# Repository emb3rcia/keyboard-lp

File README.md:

# keyboard-lp

## Description

It is my first low-profile keyboard, and first per-key GPIO keyboard. It features 2 USB ports - one for communication with PC and one for power for LEDs, per-key LED backlight and full n-key rollover!

## Why i made this project

I like making keyboards, it is my second keyboard i designed and it is very fun. I also want to use LP keyboard, but i dont have budget to buy ready-to-use one.

## What i learned

Mainly i learned even more about tight connection layout on PCB, as with per-key GPIO i needed to connect each key to its individual pin on MCU.

# Photos

# BOM

|Product                            |Description                    |Price   |Shipping                               |Amount      |Why more than needed               |Link                                              |
|-----------------------------------|-------------------------------|--------|---------------------------------------|------------|-----------------------------------|--------------------------------------------------|
|Kalih Choc v2                      |Switches                       |27.72USD|Free                                   |90          |Nearest amount more to 87 needed   |https://aliexpress.com/item/1005008175864256.html |
|Keycaps                            |Keycaps                        |14.89USD|Free                                   |118         |Its full set, cheapest I could find|https://aliexpress.com/item/1005004613625285.html |
|Stabs                              |Stabilizers                    |6.10USD |Free                                   |1x6.25u 4x2u|N/A                                |https://aliexpress.com/item/1005009331747192.html |
|TORCH C0805B104K500NT              |Decoup caps                    |0.43USD |LCSC                                   |125         |Sold in batches of 25, need 101    |https://www.lcsc.com/product-detail/C476766.html  |
|Taiyo Yuden HMK212BC7105KGHTE      |Bigger decoup caps             |0.43USD |LCSC                                   |10          |Sold in batches of 10, need 9      |https://www.lcsc.com/product-detail/C385977.html  |
|KEMET C0805C473J3GECTU             |Bulk decoup caps               |1.04USD |LCSC                                   |5           |Sold in batches of 5, need 2       |https://www.lcsc.com/product-detail/C22409503.html|
|TECH PUBLIC RCLAMP0502BATCT        |ESD diode for CC and Data lanes|0.48USD |LCSC                                   |10          |Sold in batches of 10, need 3      |https://www.lcsc.com/product-detail/C3040620.html |
|TI SN74LVC1T45DCKR                 |Level shifter                  |0.45USD |LCSC                                   |5           |Sold in batches of 5, need 1       |https://www.lcsc.com/product-detail/C9382.html    |
|SHOU HAN TYPE-C 16PIN 2MD(073)     |USB-C ports                    |1.23USD |LCSC                                   |20          |Sold in batches of 20, need 2      |https://www.lcsc.com/product-detail/C2765186.html |
|MICROCHIP MCP1726-3302E/SN         |LDO                            |2.22USD |LCSC                                   |1           |N/A                                |https://www.lcsc.com/product-detail/C635928.html  |
|OPSCO Optoelectronics SK6812MINI-YW|LED Diodes                     |14.85USD|LCSC                                   |90          |Sold in batches of 5, need 87      |https://www.lcsc.com/product-detail/C5378722.html |
|Littelfuse SMA6L5.0A               |VBUS ESD diodes                |1.57USD |LCSC                                   |2           |N/A                                |https://www.lcsc.com/product-detail/C1974860.html |
|FOJAN FRC0805J220 TS               |Data lanes resistors           |0.17USD |LCSC                                   |100         |Sold in batches of 100, need 2     |https://www.lcsc.com/product-detail/C2907310.html |
|FOJAN FRC0805J330 TS               |Level shifter→LEDs resistor    |0.17USD |LCSC                                   |100         |Sold in batches of 100, need 1     |https://www.lcsc.com/product-detail/C2907322.html |
|FOJAN FRC0805J103TS                |Boot pin pulldown resistor     |0.18USD |LCSC                                   |100         |Sold in batches of 100, need 1     |https://www.lcsc.com/product-detail/C2930231.html |
|FOJAN FRC0805J512TS                |CC resistors                   |0.17USD |LCSC                                   |100         |Sold in batches of 100, need 2     |https://www.lcsc.com/product-detail/C2930296.html |
|ST STM32G474QCT6                   |MCU                            |7.30USD |LCSC  (5.07USD for all items from LCSC)|1x6.25u 4x2u|N/A                                |https://www.lcsc.com/product-detail/C730128.html  |
|PCB from JLCPCB                    |PCB                            |54.40USD|19.14USD                               |5           |Minimal order is 5                 |https://www.jlcpcb.com                            |
|Screws                             |M2x12 flathead screws          |1.48USD |Free                                   |50          |Minimal order is 50                |https://aliexpress.com/item/1005007593731439.html |
|Total                              |97.79USD                       |74.58USD|25.21USD                               |            |                                   |                                                  |

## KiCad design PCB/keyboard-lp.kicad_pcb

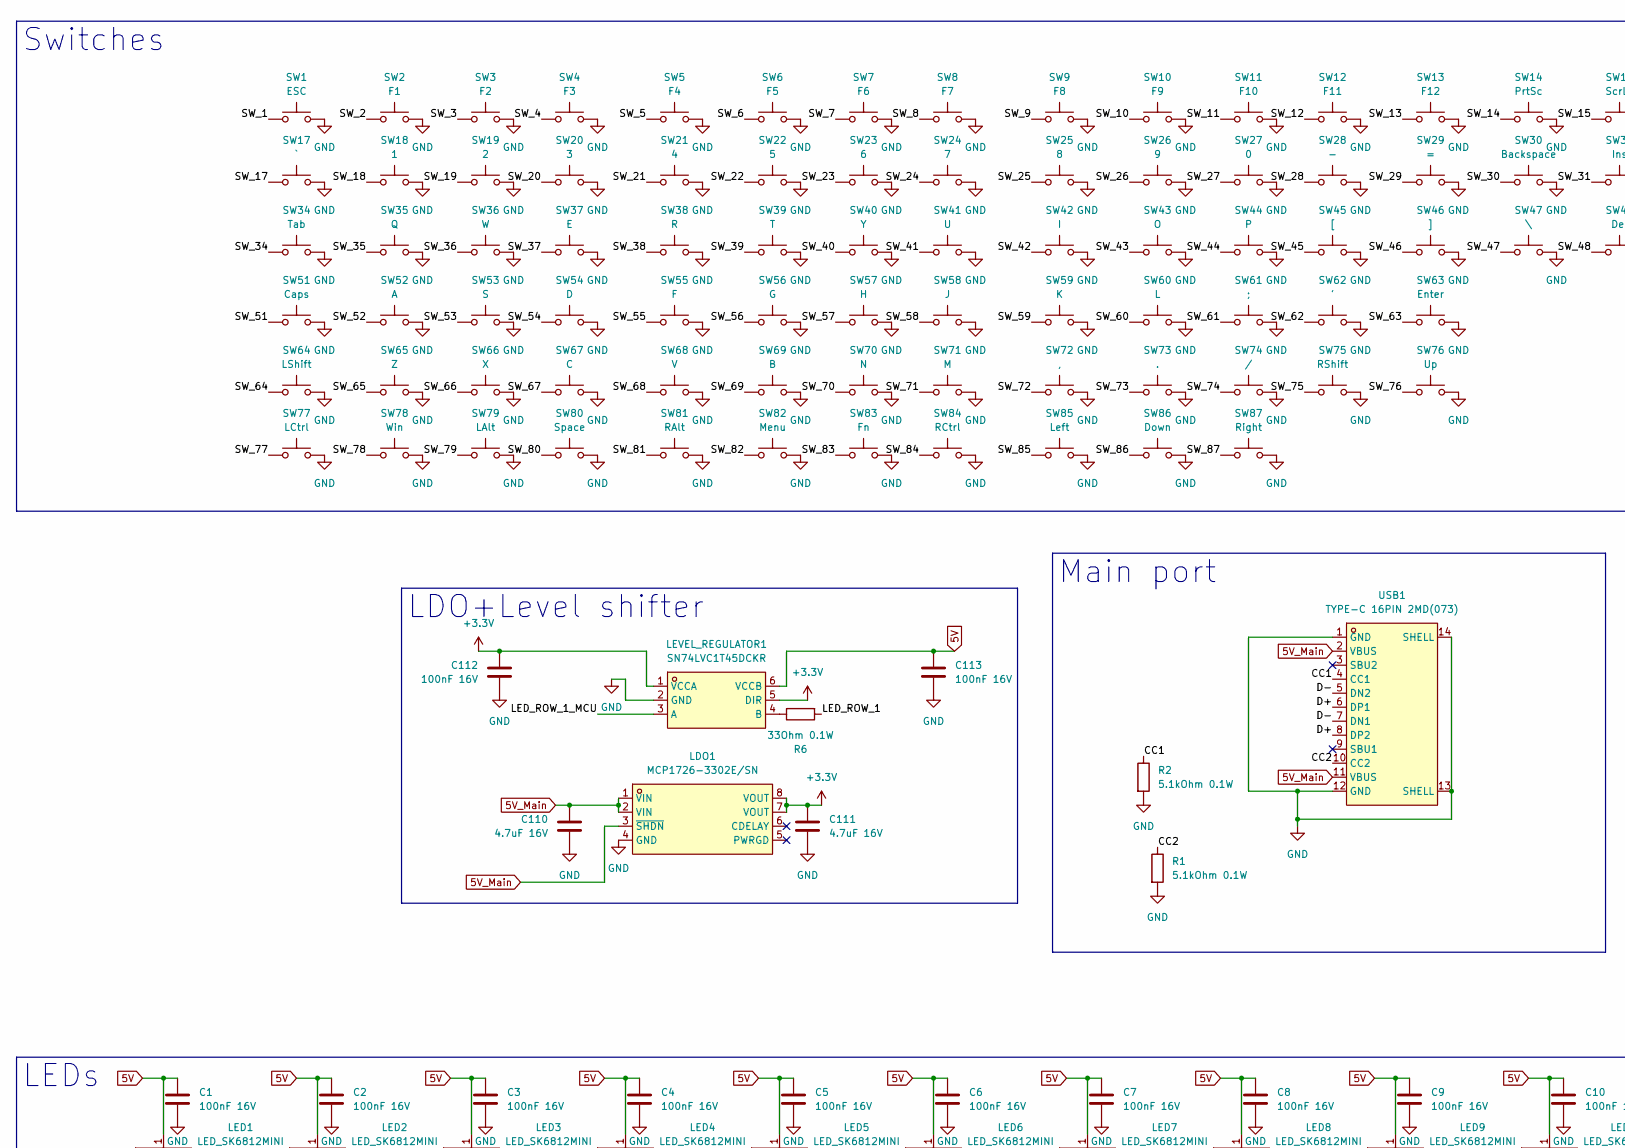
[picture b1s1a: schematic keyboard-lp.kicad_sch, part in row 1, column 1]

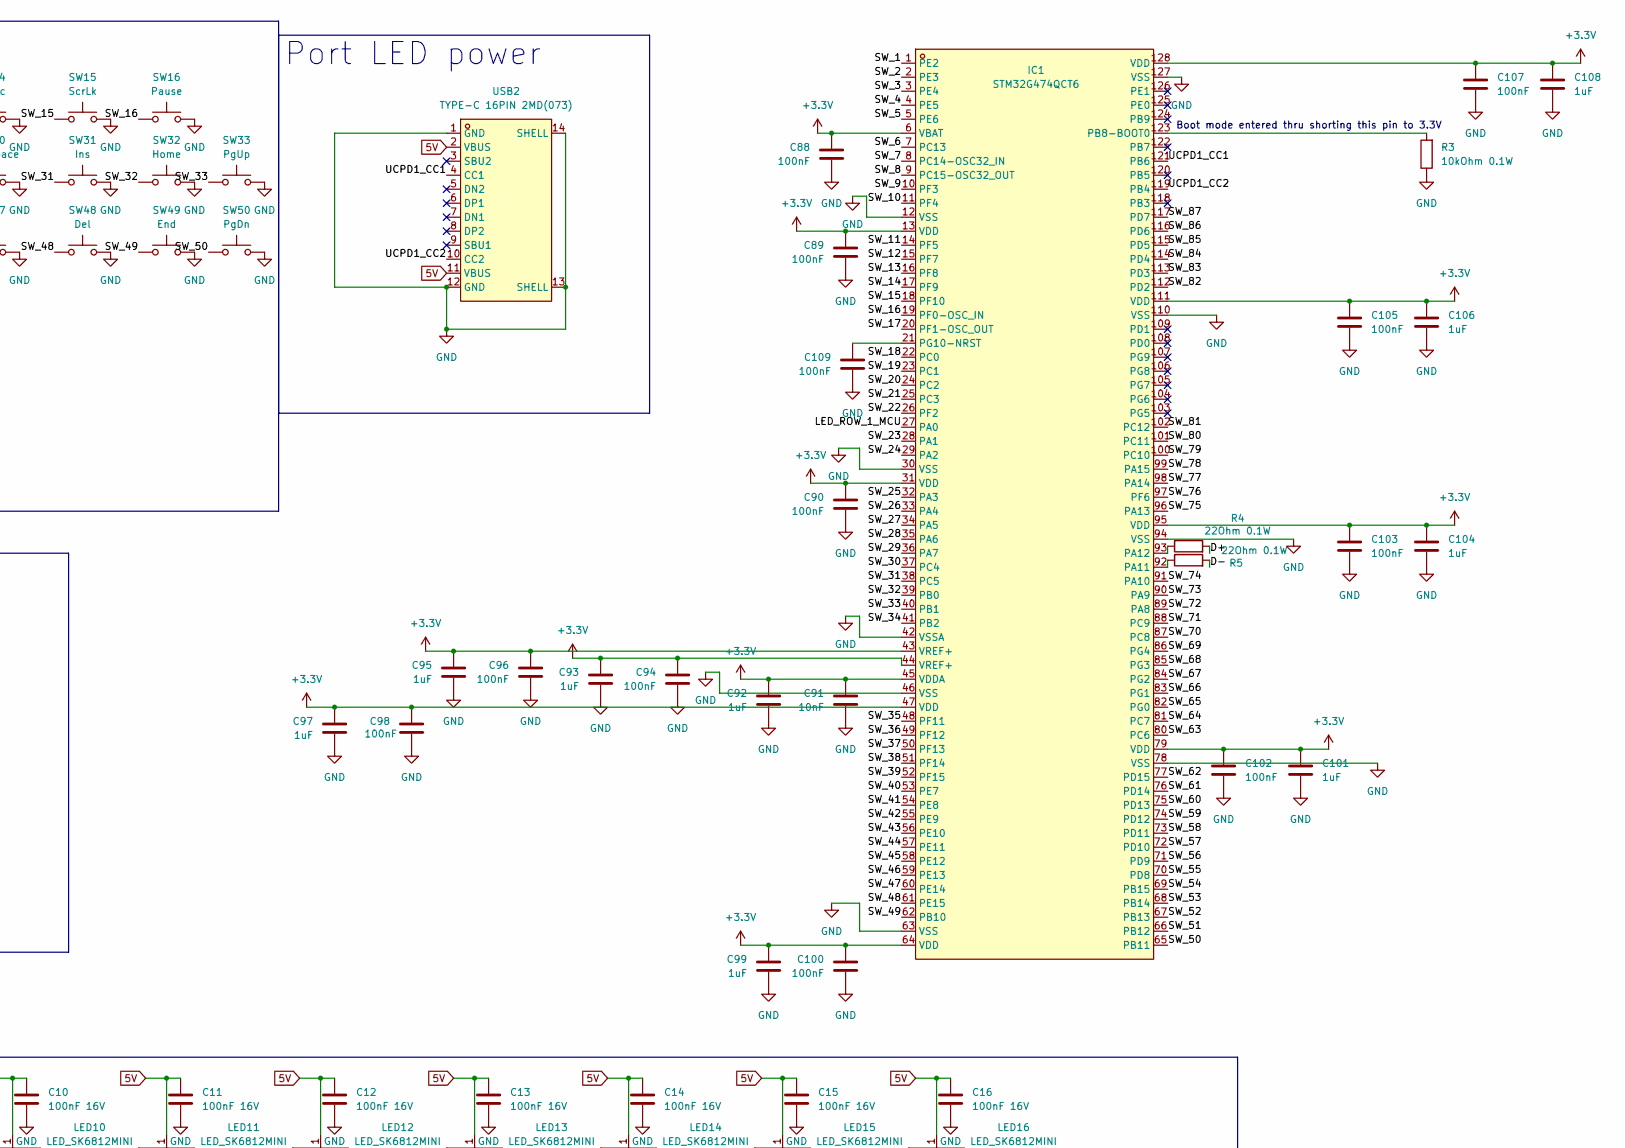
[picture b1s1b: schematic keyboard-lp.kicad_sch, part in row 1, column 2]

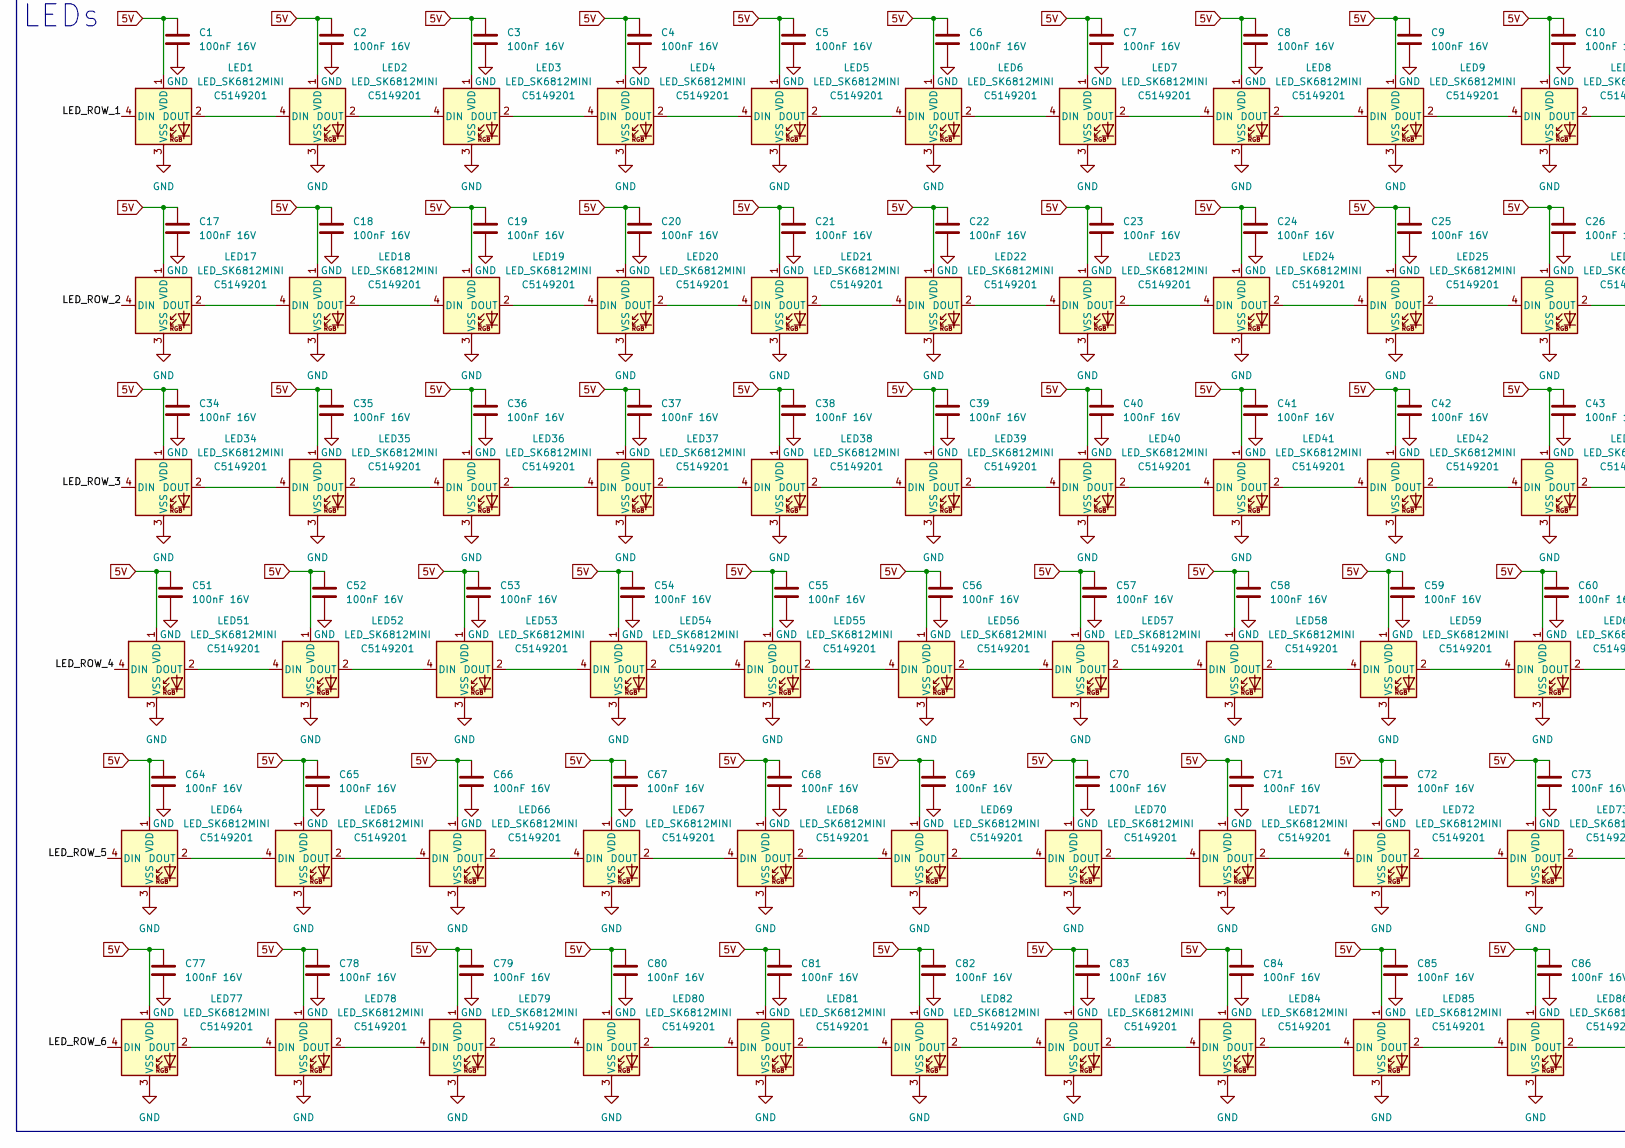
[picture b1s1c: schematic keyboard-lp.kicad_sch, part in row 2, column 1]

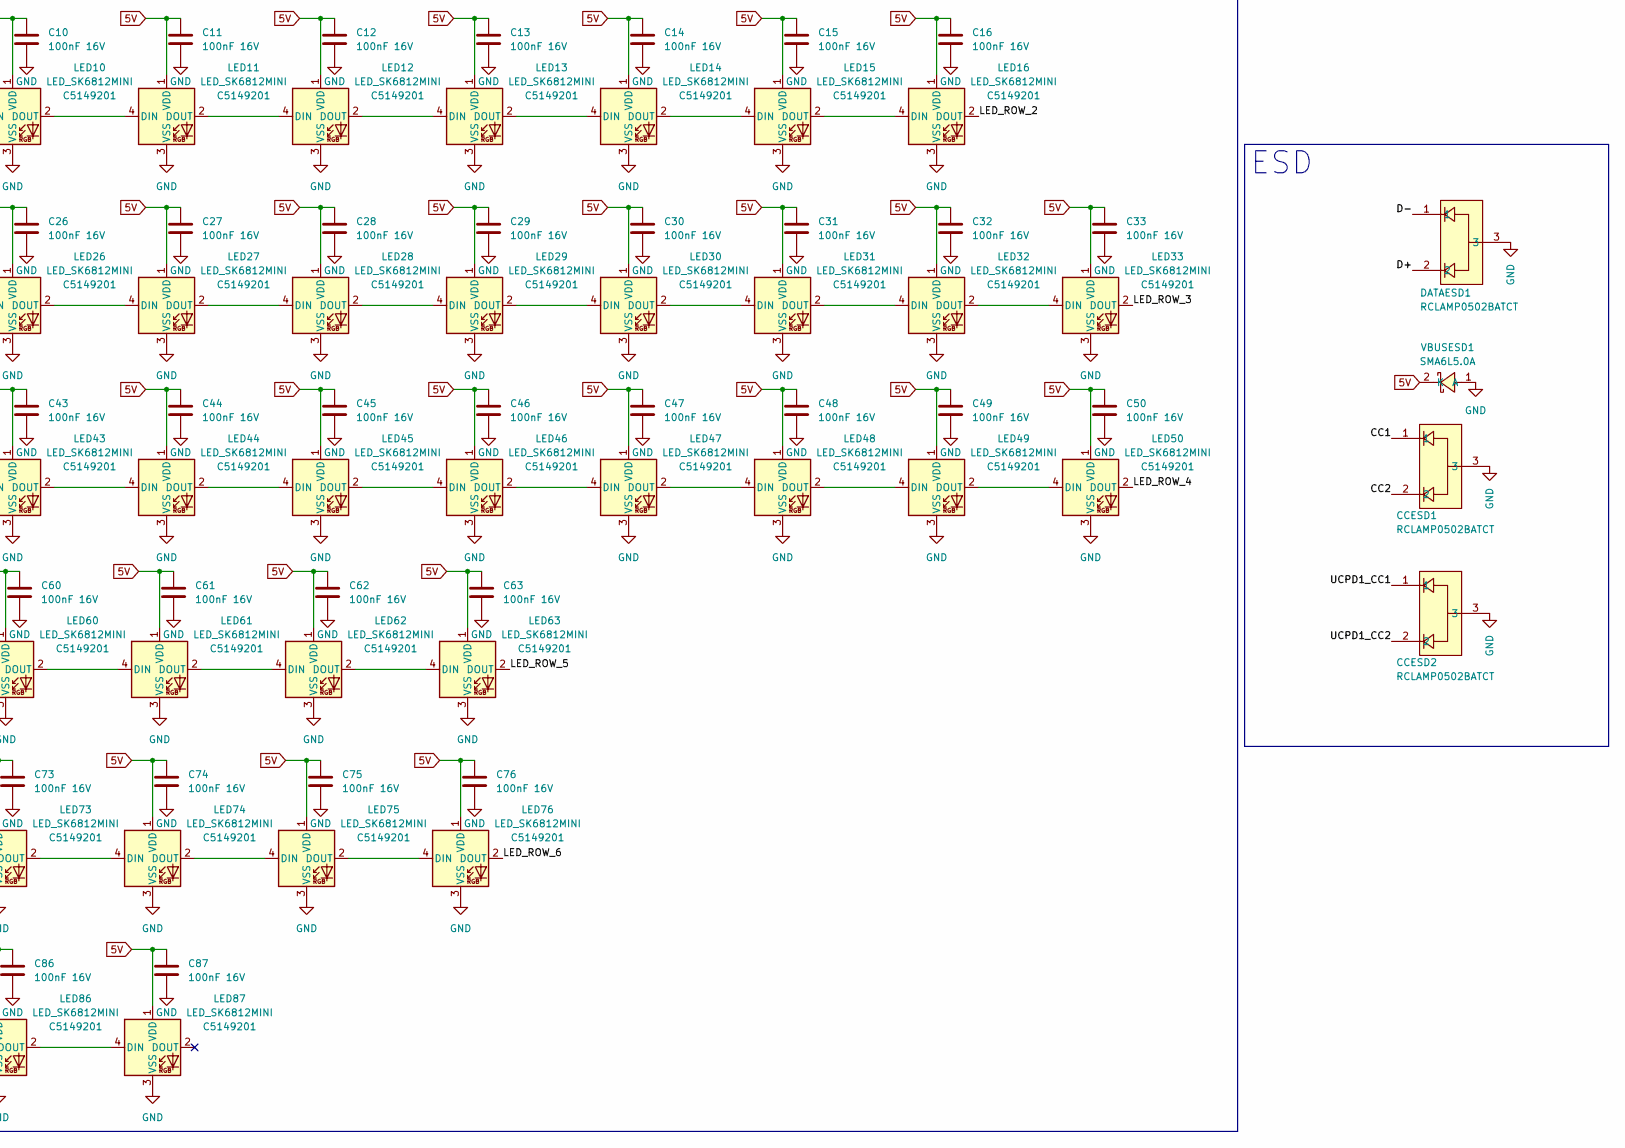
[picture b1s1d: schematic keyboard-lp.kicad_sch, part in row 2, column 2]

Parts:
C1, C2, C3, C4, C5, C6, C7, C8, C9, C10, C11, C12, C13, C14, C15, C16, C17, C18, C19, C20, C21, C22, C23, C24, C25, C26, C27, C28, C29, C30, C31, C32, C33, C34, C35, C36, C37, C38, C39, C40, C41, C42, C43, C44, C45, C46, C47, C48, C49, C50, C51, C52, C53, C54, C55, C56, C57, C58, C59, C60, C61, C62, C63, C64, C65, C66, C67, C68, C69, C70, C71, C72, C73, C74, C75, C76, C77, C78, C79, C80, C81, C82, C83, C84, C85, C86, C87, C112, C113: 100nF 16V; C_0805_2012Metric_Pad1.18x1.45mm_HandSolder
C88, C89, C90, C94, C96, C98, C100, C102, C103, C105, C107, C109: 100nF; C_0805_2012Metric_Pad1.18x1.45mm_HandSolder
C91: 10nF; C_0805_2012Metric_Pad1.18x1.45mm_HandSolder
C92, C93, C95, C97, C99, C101, C104, C106, C108: 1uF; C_0805_2012Metric_Pad1.18x1.45mm_HandSolder
C110, C111: 4.7uF 16V; C_0805_2012Metric_Pad1.18x1.45mm_HandSolder
CCESD1, CCESD2: RCLAMP0502BATCT; SC-75-3_L1.6-W0.8-P1.00-LS1.6-BR; LCSC Part C117553
DATAESD1: RCLAMP0502BATCT; SC-75-3_L1.6-W0.8-P1.00-LS1.6-BR; LCSC Part C117553
IC1: STM32G474QCT6; LQFP-128_L14.0-W14.0-P0.40-LS16.0-BL; LCSC Part C730128
LDO1: MCP1726-3302E/SN; SOIC-8_L5.0-W4.0-P1.27-LS6.1-BL; LCSC Part C635928
LED1, LED2, LED3, LED4, LED5, LED6, LED7, LED8, LED9, LED10, LED11, LED12, LED13, LED14, LED15, LED16, LED17, LED18, LED19, LED20, LED21, LED22, LED23, LED24, LED25, LED26, LED27, LED28, LED29, LED30, LED31, LED32, LED33, LED34, LED35, LED36, LED37, LED38, LED39, LED40, LED41, LED42, LED43, LED44, LED45, LED46, LED47, LED48, LED49, LED50, LED51, LED52, LED53, LED54, LED55, LED56, LED57, LED58, LED59, LED60, LED61, LED62, LED63, LED64, LED65, LED66, LED67, LED68, LED69, LED70, LED71, LED72, LED73, LED74, LED75, LED76, LED77, LED78, LED79, LED80, LED81, LED82, LED83, LED84, LED85, LED86, LED87: LED_SK6812MINI; LCSC C5149201
LEVEL_REGULATOR1: SN74LVC1T45DCKR; SC-70-6_L2.2-W1.3-P0.65-LS2.2-BR; LCSC Part C9382
R1, R2: 5.1kOhm 0.1W; R_0805_2012Metric_Pad1.20x1.40mm_HandSolder
R3: 10kOhm 0.1W; R_0805_2012Metric_Pad1.20x1.40mm_HandSolder
R4, R5: 22Ohm 0.1W; R_0805_2012Metric_Pad1.20x1.40mm_HandSolder
R6: 33Ohm 0.1W; R_0805_2012Metric_Pad1.20x1.40mm_HandSolder
SW1: ESC; Kailh-PG1353-Solderable-1U
SW2: F1; Kailh-PG1353-Solderable-1U
SW3: F2; Kailh-PG1353-Solderable-1U
SW4: F3; Kailh-PG1353-Solderable-1U
SW5: F4; Kailh-PG1353-Solderable-1U
SW6: F5; Kailh-PG1353-Solderable-1U
SW7: F6; Kailh-PG1353-Solderable-1U
SW8: F7; Kailh-PG1353-Solderable-1U
SW9: F8; Kailh-PG1353-Solderable-1U
SW10: F9; Kailh-PG1353-Solderable-1U
SW11: F10; Kailh-PG1353-Solderable-1U
SW12: F11; Kailh-PG1353-Solderable-1U
SW13: F12; Kailh-PG1353-Solderable-1U
SW14: PrtSc; Kailh-PG1353-Solderable-1U
SW15: ScrLk; Kailh-PG1353-Solderable-1U
SW16: Pause; Kailh-PG1353-Solderable-1U
SW17: `; Kailh-PG1353-Solderable-1U
SW18: 1; Kailh-PG1353-Solderable-1U
SW19: 2; Kailh-PG1353-Solderable-1U
SW20: 3; Kailh-PG1353-Solderable-1U
SW21: 4; Kailh-PG1353-Solderable-1U
SW22: 5; Kailh-PG1353-Solderable-1U
SW23: 6; Kailh-PG1353-Solderable-1U
SW24: 7; Kailh-PG1353-Solderable-1U
SW25: 8; Kailh-PG1353-Solderable-1U
SW26: 9; Kailh-PG1353-Solderable-1U
SW27: 0; Kailh-PG1353-Solderable-1U
SW28: -; Kailh-PG1353-Solderable-1U
SW29: =; Kailh-PG1353-Solderable-1U
SW30: Backspace; Kailh-PG1353-Solderable-2U
SW31: Ins; Kailh-PG1353-Solderable-1U
SW32: Home; Kailh-PG1353-Solderable-1U
SW33: PgUp; Kailh-PG1353-Solderable-1U
SW34: Tab; Kailh-PG1353-Solderable-1.5U
SW35: Q; Kailh-PG1353-Solderable-1U
SW36: W; Kailh-PG1353-Solderable-1U
SW37: E; Kailh-PG1353-Solderable-1U
SW38: R; Kailh-PG1353-Solderable-1U
SW39: T; Kailh-PG1353-Solderable-1U
SW40: Y; Kailh-PG1353-Solderable-1U
SW41: U; Kailh-PG1353-Solderable-1U
SW42: I; Kailh-PG1353-Solderable-1U
SW43: O; Kailh-PG1353-Solderable-1U
SW44: P; Kailh-PG1353-Solderable-1U
SW45: [; Kailh-PG1353-Solderable-1U
SW46: ]; Kailh-PG1353-Solderable-1U
SW47: \; Kailh-PG1353-Solderable-1.5U
SW48: Del; Kailh-PG1353-Solderable-1U
SW49: End; Kailh-PG1353-Solderable-1U
SW50: PgDn; Kailh-PG1353-Solderable-1U
SW51: Caps; Kailh-PG1353-Solderable-1.75U
SW52: A; Kailh-PG1353-Solderable-1U
SW53: S; Kailh-PG1353-Solderable-1U
SW54: D; Kailh-PG1353-Solderable-1U
SW55: F; Kailh-PG1353-Solderable-1U
SW56: G; Kailh-PG1353-Solderable-1U
SW57: H; Kailh-PG1353-Solderable-1U
SW58: J; Kailh-PG1353-Solderable-1U
SW59: K; Kailh-PG1353-Solderable-1U
SW60: L; Kailh-PG1353-Solderable-1U
SW61: ;; Kailh-PG1353-Solderable-1U
SW62: '; Kailh-PG1353-Solderable-1U
SW63: Enter; Kailh-PG1353-Solderable-2.25U
SW64: LShift; Kailh-PG1353-Solderable-2.25U
SW65: Z; Kailh-PG1353-Solderable-1U
SW66: X; Kailh-PG1353-Solderable-1U
SW67: C; Kailh-PG1353-Solderable-1U
SW68: V; Kailh-PG1353-Solderable-1U
SW69: B; Kailh-PG1353-Solderable-1U
SW70: N; Kailh-PG1353-Solderable-1U
SW71: M; Kailh-PG1353-Solderable-1U
SW72: ,; Kailh-PG1353-Solderable-1U
SW73: .; Kailh-PG1353-Solderable-1U
SW74: /; Kailh-PG1353-Solderable-1U
SW75: RShift; Kailh-PG1353-Solderable-2.75U
SW76: Up; Kailh-PG1353-Solderable-1U
SW77: LCtrl; Kailh-PG1353-Solderable-1.25U
SW78: Win; Kailh-PG1353-Solderable-1.25U
SW79: LAlt; Kailh-PG1353-Solderable-1.25U
SW80: Space; Kailh-PG1353-Solderable-6.25U
SW81: RAlt; Kailh-PG1353-Solderable-1.25U
SW82: Menu; Kailh-PG1353-Solderable-1.25U
SW83: Fn; Kailh-PG1353-Solderable-1.25U
SW84: RCtrl; Kailh-PG1353-Solderable-1.25U
SW85: Left; Kailh-PG1353-Solderable-1U
SW86: Down; Kailh-PG1353-Solderable-1U
SW87: Right; Kailh-PG1353-Solderable-1U
USB1, USB2: TYPE-C 16PIN 2MD(073); USB-C-SMD_TYPE-C-6PIN-2MD-073; LCSC Part C2765186
VBUSESD1: SMA6L5.0A; SMA_L4.3-W2.6-LS5.2-R-RD; LCSC Part C1974860

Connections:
+3.3V: C88.1, C89.1, C90.1, C91.1, C92.1, C93.1, C94.1, C95.1, C96.1, C97.1, C98.1, C99.1, C100.1, C101.1, C102.1, C103.1, C104.1, C105.1, C106.1, C107.1, C108.1, C111.1, C112.1, IC1.6 (VBAT), IC1.13 (VDD), IC1.31 (VDD), IC1.43 (VREF+), IC1.44 (VREF+), IC1.45 (VDDA), IC1.47 (VDD), IC1.64 (VDD), IC1.79 (VDD), IC1.95 (VDD), IC1.111 (VDD), IC1.128 (VDD), LDO1.7 (VOUT), LDO1.8 (VOUT), LEVEL_REGULATOR1.1 (VCCA), LEVEL_REGULATOR1.5 (DIR)
/CC1: CCESD1.1, R2.1, USB1.4 (CC1)
/CC2: CCESD1.2, R1.1, USB1.10 (CC2)
/D+: DATAESD1.2, R4.2, USB1.6 (DP1), USB1.8 (DP2)
/D-: DATAESD1.1, R5.2, USB1.5 (DN2), USB1.7 (DN1)
/LED_ROW_1: LED1.4 (DIN), R6.2
/LED_ROW_1_MCU: IC1.27 (PA0), LEVEL_REGULATOR1.3 (A)
/LED_ROW_2: LED16.2 (DOUT), LED17.4 (DIN)
/LED_ROW_3: LED33.2 (DOUT), LED34.4 (DIN)
/LED_ROW_4: LED50.2 (DOUT), LED51.4 (DIN)
/LED_ROW_5: LED63.2 (DOUT), LED64.4 (DIN)
/LED_ROW_6: LED76.2 (DOUT), LED77.4 (DIN)
/SW_1: IC1.1 (PE2), SW1.1
/SW_2: IC1.2 (PE3), SW2.1
/SW_3: IC1.3 (PE4), SW3.1
/SW_4: IC1.4 (PE5), SW4.1
/SW_5: IC1.5 (PE6), SW5.1
/SW_6: IC1.7 (PC13), SW6.1
/SW_7: IC1.8 (PC14-OSC32_IN), SW7.1
/SW_8: IC1.9 (PC15-OSC32_OUT), SW8.1
/SW_9: IC1.10 (PF3), SW9.1
/SW_10: IC1.11 (PF4), SW10.1
/SW_11: IC1.14 (PF5), SW11.1
/SW_12: IC1.15 (PF7), SW12.1
/SW_13: IC1.16 (PF8), SW13.1
/SW_14: IC1.17 (PF9), SW14.1
/SW_15: IC1.18 (PF10), SW15.1
/SW_16: IC1.19 (PF0-OSC_IN), SW16.1
/SW_17: IC1.20 (PF1-OSC_OUT), SW17.1
/SW_18: IC1.22 (PC0), SW18.1
/SW_19: IC1.23 (PC1), SW19.1
/SW_20: IC1.24 (PC2), SW20.1
/SW_21: IC1.25 (PC3), SW21.1
/SW_22: IC1.26 (PF2), SW22.1
/SW_23: IC1.28 (PA1), SW23.1
/SW_24: IC1.29 (PA2), SW24.1
/SW_25: IC1.32 (PA3), SW25.1
/SW_26: IC1.33 (PA4), SW26.1
/SW_27: IC1.34 (PA5), SW27.1
/SW_28: IC1.35 (PA6), SW28.1
/SW_29: IC1.36 (PA7), SW29.1
/SW_30: IC1.37 (PC4), SW30.1
/SW_31: IC1.38 (PC5), SW31.1
/SW_32: IC1.39 (PB0), SW32.1
/SW_33: IC1.40 (PB1), SW33.1
/SW_34: IC1.41 (PB2), SW34.1
/SW_35: IC1.48 (PF11), SW35.1
/SW_36: IC1.49 (PF12), SW36.1
/SW_37: IC1.50 (PF13), SW37.1
/SW_38: IC1.51 (PF14), SW38.1
/SW_39: IC1.52 (PF15), SW39.1
/SW_40: IC1.53 (PE7), SW40.1
/SW_41: IC1.54 (PE8), SW41.1
/SW_42: IC1.55 (PE9), SW42.1
/SW_43: IC1.56 (PE10), SW43.1
/SW_44: IC1.57 (PE11), SW44.1
/SW_45: IC1.58 (PE12), SW45.1
/SW_46: IC1.59 (PE13), SW46.1
/SW_47: IC1.60 (PE14), SW47.1
/SW_48: IC1.61 (PE15), SW48.1
/SW_49: IC1.62 (PB10), SW49.1
/SW_50: IC1.65 (PB11), SW50.1
/SW_51: IC1.66 (PB12), SW51.1
/SW_52: IC1.67 (PB13), SW52.1
/SW_53: IC1.68 (PB14), SW53.1
/SW_54: IC1.69 (PB15), SW54.1
/SW_55: IC1.70 (PD8), SW55.1
/SW_56: IC1.71 (PD9), SW56.1
/SW_57: IC1.72 (PD10), SW57.1
/SW_58: IC1.73 (PD11), SW58.1
/SW_59: IC1.74 (PD12), SW59.1
/SW_60: IC1.75 (PD13), SW60.1
/SW_61: IC1.76 (PD14), SW61.1
/SW_62: IC1.77 (PD15), SW62.1
/SW_63: IC1.80 (PC6), SW63.1
/SW_64: IC1.81 (PC7), SW64.1
/SW_65: IC1.82 (PG0), SW65.1
/SW_66: IC1.83 (PG1), SW66.1
/SW_67: IC1.84 (PG2), SW67.1
/SW_68: IC1.85 (PG3), SW68.1
/SW_69: IC1.86 (PG4), SW69.1
/SW_70: IC1.87 (PC8), SW70.1
/SW_71: IC1.88 (PC9), SW71.1
/SW_72: IC1.89 (PA8), SW72.1
/SW_73: IC1.90 (PA9), SW73.1
/SW_74: IC1.91 (PA10), SW74.1
/SW_75: IC1.96 (PA13), SW75.1
/SW_76: IC1.97 (PF6), SW76.1
/SW_77: IC1.98 (PA14), SW77.1
/SW_78: IC1.99 (PA15), SW78.1
/SW_79: IC1.100 (PC10), SW79.1
/SW_80: IC1.101 (PC11), SW80.1
/SW_81: IC1.102 (PC12), SW81.1
/SW_82: IC1.112 (PD2), SW82.1
/SW_83: IC1.113 (PD3), SW83.1
/SW_84: IC1.114 (PD4), SW84.1
/SW_85: IC1.115 (PD5), SW85.1
/SW_86: IC1.116 (PD6), SW86.1
/SW_87: IC1.117 (PD7), SW87.1
/UCPD1_CC1: CCESD2.1, IC1.121 (PB6), USB2.4 (CC1)
/UCPD1_CC2: CCESD2.2, IC1.119 (PB4), USB2.10 (CC2)
GND: C1.2, C2.2, C3.2, C4.2, C5.2, C6.2, C7.2, C8.2, C9.2, C10.2, C11.2, C12.2, C13.2, C14.2, C15.2, C16.2, C17.2, C18.2, C19.2, C20.2, C21.2, C22.2, C23.2, C24.2, C25.2, C26.2, C27.2, C28.2, C29.2, C30.2, C31.2, C32.2, C33.2, C34.2, C35.2, C36.2, C37.2, C38.2, C39.2, C40.2, C41.2, C42.2, C43.2, C44.2, C45.2, C46.2, C47.2, C48.2, C49.2, C50.2, C51.2, C52.2, C53.2, C54.2, C55.2, C56.2, C57.2, C58.2, C59.2, C60.2, C61.2, C62.2, C63.2, C64.2, C65.2, C66.2, C67.2, C68.2, C69.2, C70.2, C71.2, C72.2, C73.2, C74.2, C75.2, C76.2, C77.2, C78.2, C79.2, C80.2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; also elsewhere on the board
unnamed: IC1.92 (PA11), R5.1
unnamed: IC1.93 (PA12), R4.1
unnamed: IC1.123 (PB8-BOOT0), R3.2
unnamed: C109.1, IC1.21 (PG10-NRST)
unnamed: LED1.2 (DOUT), LED2.4 (DIN)
unnamed: LED2.2 (DOUT), LED3.4 (DIN)
unnamed: LED3.2 (DOUT), LED4.4 (DIN)
unnamed: LED4.2 (DOUT), LED5.4 (DIN)
unnamed: LED5.2 (DOUT), LED6.4 (DIN)
unnamed: LED6.2 (DOUT), LED7.4 (DIN)
unnamed: LED7.2 (DOUT), LED8.4 (DIN)
unnamed: LED8.2 (DOUT), LED9.4 (DIN)
unnamed: LED9.2 (DOUT), LED10.4 (DIN)
unnamed: LED10.2 (DOUT), LED11.4 (DIN)
unnamed: LED11.2 (DOUT), LED12.4 (DIN)
unnamed: LED12.2 (DOUT), LED13.4 (DIN)
unnamed: LED13.2 (DOUT), LED14.4 (DIN)
unnamed: LED14.2 (DOUT), LED15.4 (DIN)
unnamed: LED15.2 (DOUT), LED16.4 (DIN)
unnamed: LED17.2 (DOUT), LED18.4 (DIN)
unnamed: LED18.2 (DOUT), LED19.4 (DIN)
unnamed: LED19.2 (DOUT), LED20.4 (DIN)
unnamed: LED20.2 (DOUT), LED21.4 (DIN)
unnamed: LED21.2 (DOUT), LED22.4 (DIN)
unnamed: LED22.2 (DOUT), LED23.4 (DIN)
unnamed: LED23.2 (DOUT), LED24.4 (DIN)
unnamed: LED24.2 (DOUT), LED25.4 (DIN)
unnamed: LED25.2 (DOUT), LED26.4 (DIN)
unnamed: LED26.2 (DOUT), LED27.4 (DIN)
unnamed: LED27.2 (DOUT), LED28.4 (DIN)
unnamed: LED28.2 (DOUT), LED29.4 (DIN)
unnamed: LED29.2 (DOUT), LED30.4 (DIN)
unnamed: LED30.2 (DOUT), LED31.4 (DIN)
unnamed: LED31.2 (DOUT), LED32.4 (DIN)
unnamed: LED32.2 (DOUT), LED33.4 (DIN)
unnamed: LED34.2 (DOUT), LED35.4 (DIN)
unnamed: LED35.2 (DOUT), LED36.4 (DIN)
unnamed: LED36.2 (DOUT), LED37.4 (DIN)
unnamed: LED37.2 (DOUT), LED38.4 (DIN)
unnamed: LED38.2 (DOUT), LED39.4 (DIN)
unnamed: LED39.2 (DOUT), LED40.4 (DIN)
unnamed: LED40.2 (DOUT), LED41.4 (DIN)
unnamed: LED41.2 (DOUT), LED42.4 (DIN)
unnamed: LED42.2 (DOUT), LED43.4 (DIN)
unnamed: LED43.2 (DOUT), LED44.4 (DIN)
unnamed: LED44.2 (DOUT), LED45.4 (DIN)
unnamed: LED45.2 (DOUT), LED46.4 (DIN)
unnamed: LED46.2 (DOUT), LED47.4 (DIN)
unnamed: LED47.2 (DOUT), LED48.4 (DIN)
unnamed: LED48.2 (DOUT), LED49.4 (DIN)
unnamed: LED49.2 (DOUT), LED50.4 (DIN)
unnamed: LED51.2 (DOUT), LED52.4 (DIN)
unnamed: LED52.2 (DOUT), LED53.4 (DIN)
unnamed: LED53.2 (DOUT), LED54.4 (DIN)
unnamed: LED54.2 (DOUT), LED55.4 (DIN)
unnamed: LED55.2 (DOUT), LED56.4 (DIN)
unnamed: LED56.2 (DOUT), LED57.4 (DIN)
unnamed: LED57.2 (DOUT), LED58.4 (DIN)
unnamed: LED58.2 (DOUT), LED59.4 (DIN)
unnamed: LED59.2 (DOUT), LED60.4 (DIN)
unnamed: LED60.2 (DOUT), LED61.4 (DIN)
unnamed: LED61.2 (DOUT), LED62.4 (DIN)
unnamed: LED62.2 (DOUT), LED63.4 (DIN)
unnamed: LED64.2 (DOUT), LED65.4 (DIN)
unnamed: LED65.2 (DOUT), LED66.4 (DIN)
unnamed: LED66.2 (DOUT), LED67.4 (DIN)
unnamed: LED67.2 (DOUT), LED68.4 (DIN)
unnamed: LED68.2 (DOUT), LED69.4 (DIN)
unnamed: LED69.2 (DOUT), LED70.4 (DIN)
unnamed: LED70.2 (DOUT), LED71.4 (DIN)
unnamed: LED71.2 (DOUT), LED72.4 (DIN)
unnamed: LED72.2 (DOUT), LED73.4 (DIN)
unnamed: LED73.2 (DOUT), LED74.4 (DIN)
unnamed: LED74.2 (DOUT), LED75.4 (DIN)
unnamed: LED75.2 (DOUT), LED76.4 (DIN)
unnamed: LED77.2 (DOUT), LED78.4 (DIN)
unnamed: LED78.2 (DOUT), LED79.4 (DIN)
unnamed: LED79.2 (DOUT), LED80.4 (DIN)
unnamed: LED80.2 (DOUT), LED81.4 (DIN)
unnamed: LED81.2 (DOUT), LED82.4 (DIN)
unnamed: LED82.2 (DOUT), LED83.4 (DIN)
unnamed: LED83.2 (DOUT), LED84.4 (DIN)
unnamed: LED84.2 (DOUT), LED85.4 (DIN)
unnamed: LED85.2 (DOUT), LED86.4 (DIN)
unnamed: LED86.2 (DOUT), LED87.4 (DIN)
unnamed: LEVEL_REGULATOR1.4 (B), R6.1

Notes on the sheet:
Boot mode entered thru shorting this pin to 3.3V
Main port
Port LED power
Switches
LDO+Level shifter
LEDs
ESD

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
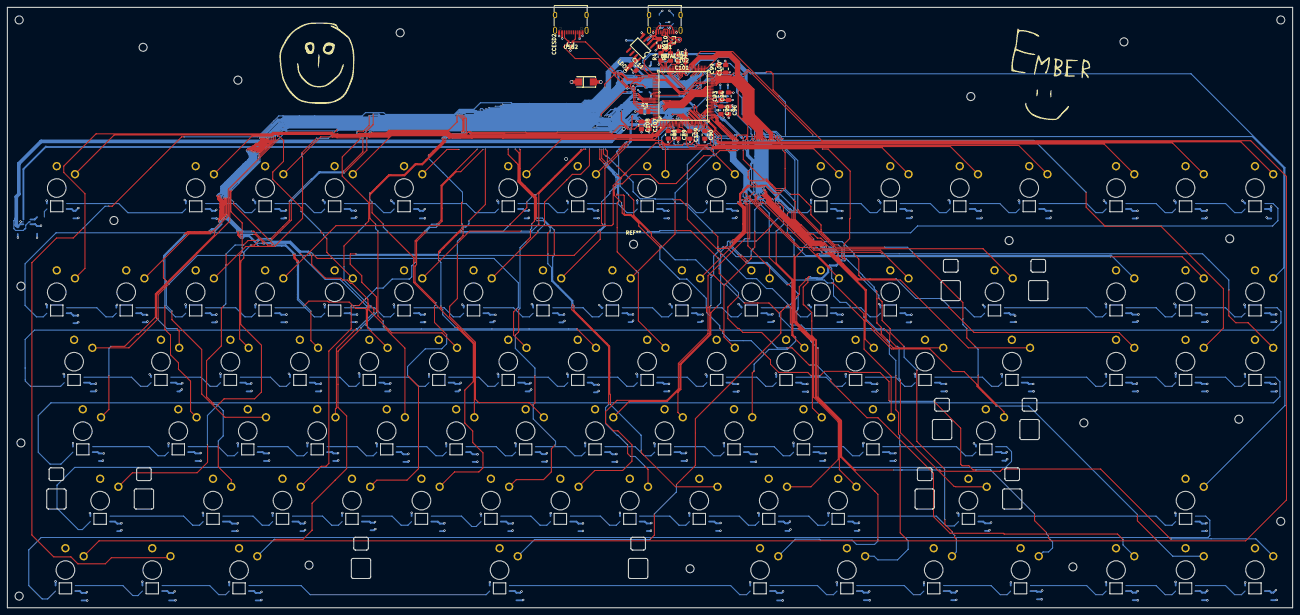
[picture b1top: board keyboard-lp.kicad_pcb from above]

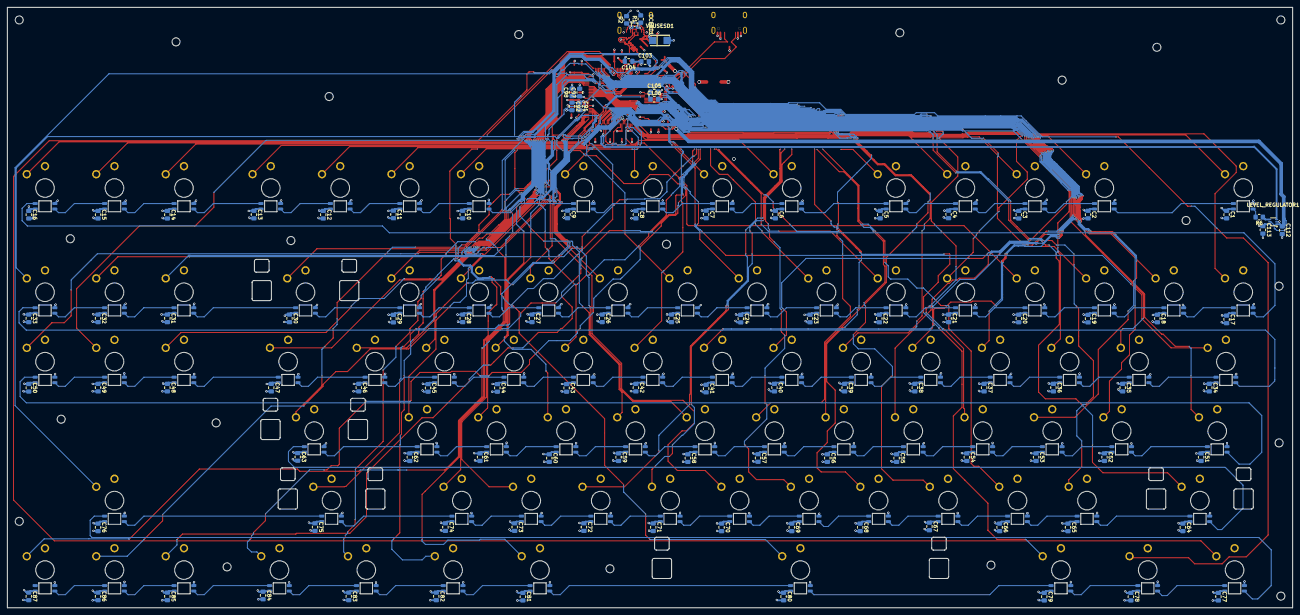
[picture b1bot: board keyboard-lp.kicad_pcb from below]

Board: 4 copper layers, 352.5 x 164.6 mm, 303 parts (190 on the bottom side), 190 nets.

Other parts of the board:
VBUSESD2: SMA6L5.0A; SMA_L4.3-W2.6-LS5.2-R-RD

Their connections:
GND: VBUSESD2.1 (A); also elsewhere on the board

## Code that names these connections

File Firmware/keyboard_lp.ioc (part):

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Mcu.Name=STM32G474Q(B-C-E)Tx
Mcu.Package=LQFP128
Mcu.UserName=STM32G474QCTx
PA0.GPIOParameters=GPIO_Speed
PA0.GPIO_Speed=GPIO_SPEED_FREQ_VERY_HIGH
PA0.Signal=S_TIM2_CH1
PA1.GPIOParameters=GPIO_PuPd,GPIO_Label
PA1.GPIO_Label=Key6_23
PA1.GPIO_PuPd=GPIO_PULLUP
PA1.Signal=GPIO_Input
PA10.GPIOParameters=GPIO_PuPd,GPIO_Label
PA10.GPIO_Label=Key/_74
PA10.GPIO_PuPd=GPIO_PULLUP
PA10.Signal=GPIO_Input
PA11.Mode=Device
PA11.Signal=USB_DM
PA12.Mode=Device
PA12.Signal=USB_DP
PA13.GPIOParameters=GPIO_PuPd,GPIO_Label
PA13.GPIO_Label=RShift_75
PA13.GPIO_PuPd=GPIO_PULLUP
PA13.Signal=GPIO_Input
PA14.GPIOParameters=GPIO_PuPd,GPIO_Label
PA14.GPIO_Label=LCtrl_77
PA14.GPIO_PuPd=GPIO_PULLUP
PA14.Signal=GPIO_Input
PA15.GPIOParameters=GPIO_PuPd,GPIO_Label
PA15.GPIO_Label=Win_78
PA15.GPIO_PuPd=GPIO_PULLUP
PA15.Signal=GPIO_Input
PA2.GPIOParameters=GPIO_PuPd,GPIO_Label
PA2.GPIO_Label=Key7_24
PA2.GPIO_PuPd=GPIO_PULLUP
PA2.Signal=GPIO_Input
PA3.GPIOParameters=GPIO_PuPd,GPIO_Label
PA3.GPIO_Label=Key8_25
PA3.GPIO_PuPd=GPIO_PULLUP
PA3.Signal=GPIO_Input
PA4.GPIOParameters=GPIO_PuPd,GPIO_Label
PA4.GPIO_Label=Key9_26
PA4.GPIO_PuPd=GPIO_PULLUP
PA4.Signal=GPIO_Input
PA5.GPIOParameters=GPIO_PuPd,GPIO_Label
PA5.GPIO_Label=Key0_27
PA5.GPIO_PuPd=GPIO_PULLUP
PA5.Signal=GPIO_Input
PA6.GPIOParameters=GPIO_PuPd,GPIO_Label
PA6.GPIO_Label=Minus_28
PA6.GPIO_PuPd=GPIO_PULLUP
PA6.Signal=GPIO_Input
PA7.GPIOParameters=GPIO_PuPd,GPIO_Label
PA7.GPIO_Label=Plus_29
PA7.GPIO_PuPd=GPIO_PULLUP
PA7.Signal=GPIO_Input
PA8.GPIOParameters=GPIO_PuPd,GPIO_Label
PA8.GPIO_Label=Key<_72
PA8.GPIO_PuPd=GPIO_PULLUP
PA8.Signal=GPIO_Input
PA9.GPIOParameters=GPIO_PuPd,GPIO_Label
PA9.GPIO_Label=Key>_73
PA9.GPIO_PuPd=GPIO_PULLUP
PA9.Signal=GPIO_Input
PB0.GPIOParameters=GPIO_PuPd,GPIO_Label
PB0.GPIO_Label=Home_32
PB0.GPIO_PuPd=GPIO_PULLUP
PB0.Signal=GPIO_Input
PB1.GPIOParameters=GPIO_PuPd,GPIO_Label
PB1.GPIO_Label=PgUp_33
PB1.GPIO_PuPd=GPIO_PULLUP
PB1.Signal=GPIO_Input
PB10.GPIOParameters=GPIO_PuPd,GPIO_Label
PB10.GPIO_Label=End_49
PB10.GPIO_PuPd=GPIO_PULLUP
PB10.Signal=GPIO_Input
PB11.GPIOParameters=GPIO_PuPd,GPIO_Label
PB11.GPIO_Label=PgDn_50
PB11.GPIO_PuPd=GPIO_PULLUP
PB11.Signal=GPIO_Input
PB12.GPIOParameters=GPIO_PuPd,GPIO_Label
PB12.GPIO_Label=Caps_51
PB12.GPIO_PuPd=GPIO_PULLUP
PB12.Signal=GPIO_Input
PB13.GPIOParameters=GPIO_PuPd,GPIO_Label
PB13.GPIO_Label=A_52
PB13.GPIO_PuPd=GPIO_PULLUP
PB13.Signal=GPIO_Input
PB14.GPIOParameters=GPIO_PuPd,GPIO_Label
PB14.GPIO_Label=S_53
PB14.GPIO_PuPd=GPIO_PULLUP
PB14.Signal=GPIO_Input
PB15.GPIOParameters=GPIO_PuPd,GPIO_Label
PB15.GPIO_Label=D_54
PB15.GPIO_PuPd=GPIO_PULLUP
PB15.Signal=GPIO_Input
PB2.GPIOParameters=GPIO_PuPd,GPIO_Label
PB2.GPIO_Label=Tab_34
PB2.GPIO_PuPd=GPIO_PULLUP
PB2.Signal=GPIO_Input
PB4.Mode=Sink_AllSignals
PB4.Signal=UCPD1_CC2
PB6.Mode=Sink_AllSignals
PB6.Signal=UCPD1_CC1
PC0.GPIOParameters=GPIO_PuPd,GPIO_Label
PC0.GPIO_Label=Key1_18
PC0.GPIO_PuPd=GPIO_PULLUP
PC0.Signal=GPIO_Input
PC1.GPIOParameters=GPIO_PuPd,GPIO_Label
PC1.GPIO_Label=Key2_19
PC1.GPIO_PuPd=GPIO_PULLUP
PC1.Signal=GPIO_Input
PC10.GPIOParameters=GPIO_PuPd,GPIO_Label
PC10.GPIO_Label=LAlt_79
PC10.GPIO_PuPd=GPIO_PULLUP
PC10.Signal=GPIO_Input
PC11.GPIOParameters=GPIO_PuPd,GPIO_Label
PC11.GPIO_Label=Space_80
PC11.GPIO_PuPd=GPIO_PULLUP
PC11.Signal=GPIO_Input
PC12.GPIOParameters=GPIO_PuPd,GPIO_Label
PC12.GPIO_Label=RAlt_81
PC12.GPIO_PuPd=GPIO_PULLUP
PC12.Signal=GPIO_Input
PC13.GPIOParameters=GPIO_PuPd,GPIO_Label
PC13.GPIO_Label=F5_6
PC13.GPIO_PuPd=GPIO_PULLUP
PC13.Signal=GPIO_Input
PC14-OSC32_IN.GPIOParameters=GPIO_PuPd,GPIO_Label
PC14-OSC32_IN.GPIO_Label=F6_7
PC14-OSC32_IN.GPIO_PuPd=GPIO_PULLUP
PC14-OSC32_IN.Signal=GPIO_Input
PC15-OSC32_OUT.GPIOParameters=GPIO_PuPd,GPIO_Label
PC15-OSC32_OUT.GPIO_Label=F7_8
PC15-OSC32_OUT.GPIO_PuPd=GPIO_PULLUP
PC15-OSC32_OUT.Signal=GPIO_Input
PC2.GPIOParameters=GPIO_PuPd,GPIO_Label
PC2.GPIO_Label=Key3_20
PC2.GPIO_PuPd=GPIO_PULLUP
PC2.Signal=GPIO_Input
PC3.GPIOParameters=GPIO_PuPd,GPIO_Label
PC3.GPIO_Label=Key4_21
PC3.GPIO_PuPd=GPIO_PULLUP
PC3.Signal=GPIO_Input
PC4.GPIOParameters=GPIO_PuPd,GPIO_Label
PC4.GPIO_Label=Backspace_30
PC4.GPIO_PuPd=GPIO_PULLUP
PC4.Signal=GPIO_Input
PC5.GPIOParameters=GPIO_PuPd,GPIO_Label
PC5.GPIO_Label=Insert_31
PC5.GPIO_PuPd=GPIO_PULLUP
PC5.Signal=GPIO_Input
PC6.GPIOParameters=GPIO_PuPd,GPIO_Label
PC6.GPIO_Label=Enter_63
PC6.GPIO_PuPd=GPIO_PULLUP
PC6.Signal=GPIO_Input
PC7.GPIOParameters=GPIO_PuPd,GPIO_Label
PC7.GPIO_Label=LShift_64
PC7.GPIO_PuPd=GPIO_PULLUP
PC7.Signal=GPIO_Input
PC8.GPIOParameters=GPIO_PuPd,GPIO_Label
PC8.GPIO_Label=N_70
PC8.GPIO_PuPd=GPIO_PULLUP
PC8.Signal=GPIO_Input
PC9.GPIOParameters=GPIO_PuPd,GPIO_Label
PC9.GPIO_Label=M_71
PC9.GPIO_PuPd=GPIO_PULLUP
PC9.Signal=GPIO_Input
PD10.GPIOParameters=GPIO_PuPd,GPIO_Label
PD10.GPIO_Label=H_57
PD10.GPIO_PuPd=GPIO_PULLUP
PD10.Signal=GPIO_Input
PD11.GPIOParameters=GPIO_PuPd,GPIO_Label
PD11.GPIO_Label=J_58
PD11.GPIO_PuPd=GPIO_PULLUP
PD11.Signal=GPIO_Input
PD12.GPIOParameters=GPIO_PuPd,GPIO_Label
PD12.GPIO_Label=K_59
PD12.GPIO_PuPd=GPIO_PULLUP
PD12.Signal=GPIO_Input
PD13.GPIOParameters=GPIO_PuPd,GPIO_Label
PD13.GPIO_Label=L_60
PD13.GPIO_PuPd=GPIO_PULLUP
PD13.Signal=GPIO_Input
PD14.GPIOParameters=GPIO_PuPd,GPIO_Label
PD14.GPIO_Label=Key\:_61
PD14.GPIO_PuPd=GPIO_PULLUP
PD14.Signal=GPIO_Input
PD15.GPIOParameters=GPIO_PuPd,GPIO_Label
PD15.GPIO_Label=Key"_62
PD15.GPIO_PuPd=GPIO_PULLUP
PD15.Signal=GPIO_Input
PD2.GPIOParameters=GPIO_Label,GPIO_PuPd
PD2.GPIO_Label=Menu_82
PD2.GPIO_PuPd=GPIO_PULLUP
PD2.Signal=GPIO_Input
PD3.GPIOParameters=GPIO_Label,GPIO_PuPd
PD3.GPIO_Label=Fn_83
PD3.GPIO_PuPd=GPIO_PULLUP
PD3.Signal=GPIO_Input
PD4.GPIOParameters=GPIO_Label,GPIO_PuPd
PD4.GPIO_Label=RCtrl_84
PD4.GPIO_PuPd=GPIO_PULLUP
PD4.Signal=GPIO_Input
PD5.GPIOParameters=GPIO_Label,GPIO_PuPd
PD5.GPIO_Label=Left_85
PD5.GPIO_PuPd=GPIO_PULLUP
PD5.Signal=GPIO_Input
PD6.GPIOParameters=GPIO_Label,GPIO_PuPd
PD6.GPIO_Label=Down_86
PD6.GPIO_PuPd=GPIO_PULLUP
PD6.Signal=GPIO_Input
PD7.GPIOParameters=GPIO_Label,GPIO_PuPd
PD7.GPIO_Label=Right_87
PD7.GPIO_PuPd=GPIO_PULLUP
PD7.Signal=GPIO_Input
PD8.GPIOParameters=GPIO_PuPd,GPIO_Label
PD8.GPIO_Label=F_55
PD8.GPIO_PuPd=GPIO_PULLUP
PD8.Signal=GPIO_Input
PD9.GPIOParameters=GPIO_PuPd,GPIO_Label
PD9.GPIO_Label=G_56
PD9.GPIO_PuPd=GPIO_PULLUP
PD9.Signal=GPIO_Input
PE10.GPIOParameters=GPIO_PuPd,GPIO_Label
PE10.GPIO_Label=O_43
PE10.GPIO_PuPd=GPIO_PULLUP
PE10.Signal=GPIO_Input
PE11.GPIOParameters=GPIO_PuPd,GPIO_Label
PE11.GPIO_Label=P_44
PE11.GPIO_PuPd=GPIO_PULLUP
PE11.Signal=GPIO_Input
PE12.GPIOParameters=GPIO_PuPd,GPIO_Label
PE12.GPIO_Label=Key[_45
PE12.GPIO_PuPd=GPIO_PULLUP
PE12.Signal=GPIO_Input
PE13.GPIOParameters=GPIO_PuPd,GPIO_Label
PE13.GPIO_Label=Key]_46
PE13.GPIO_PuPd=GPIO_PULLUP
PE13.Signal=GPIO_Input
PE14.GPIOParameters=GPIO_PuPd,GPIO_Label
PE14.GPIO_Label=Key\\_47
PE14.GPIO_PuPd=GPIO_PULLUP
PE14.Signal=GPIO_Input
PE15.GPIOParameters=GPIO_PuPd,GPIO_Label
PE15.GPIO_Label=Delete_48
PE15.GPIO_PuPd=GPIO_PULLUP
PE15.Signal=GPIO_Input
PE2.GPIOParameters=GPIO_PuPd,GPIO_Label
PE2.GPIO_Label=ESC_1
PE2.GPIO_PuPd=GPIO_PULLUP
PE2.Signal=GPIO_Input
PE3.GPIOParameters=GPIO_PuPd,GPIO_Label
PE3.GPIO_Label=F1_2
PE3.GPIO_PuPd=GPIO_PULLUP
PE3.Signal=GPIO_Input
PE4.GPIOParameters=GPIO_PuPd,GPIO_Label
PE4.GPIO_Label=F2_3
PE4.GPIO_PuPd=GPIO_PULLUP
PE4.Signal=GPIO_Input
PE5.GPIOParameters=GPIO_PuPd,GPIO_Label
PE5.GPIO_Label=F3_4
PE5.GPIO_PuPd=GPIO_PULLUP
PE5.Signal=GPIO_Input
PE6.GPIOParameters=GPIO_PuPd,GPIO_Label
PE6.GPIO_Label=F4_5
PE6.GPIO_PuPd=GPIO_PULLUP
PE6.Signal=GPIO_Input
PE7.GPIOParameters=GPIO_PuPd,GPIO_Label
PE7.GPIO_Label=Y_40
PE7.GPIO_PuPd=GPIO_PULLUP
PE7.Signal=GPIO_Input
PE8.GPIOParameters=GPIO_PuPd,GPIO_Label
PE8.GPIO_Label=U_41
PE8.GPIO_PuPd=GPIO_PULLUP
PE8.Signal=GPIO_Input
PE9.GPIOParameters=GPIO_PuPd,GPIO_Label
PE9.GPIO_Label=I_42
PE9.GPIO_PuPd=GPIO_PULLUP
PE9.Signal=GPIO_Input
PF0-OSC_IN.GPIOParameters=GPIO_PuPd,GPIO_Label
PF0-OSC_IN.GPIO_Label=Pause_16
PF0-OSC_IN.GPIO_PuPd=GPIO_PULLUP
PF0-OSC_IN.Signal=GPIO_Input
PF1-OSC_OUT.GPIOParameters=GPIO_PuPd,GPIO_Label
PF1-OSC_OUT.GPIO_Label=Grave_17
PF1-OSC_OUT.GPIO_PuPd=GPIO_PULLUP
PF1-OSC_OUT.Signal=GPIO_Input
PF10.GPIOParameters=GPIO_PuPd,GPIO_Label
PF10.GPIO_Label=ScrLk_15
PF10.GPIO_PuPd=GPIO_PULLUP
PF10.Signal=GPIO_Input
PF11.GPIOParameters=GPIO_PuPd,GPIO_Label
PF11.GPIO_Label=Q_35
PF11.GPIO_PuPd=GPIO_PULLUP
PF11.Signal=GPIO_Input
PF12.GPIOParameters=GPIO_PuPd,GPIO_Label
PF12.GPIO_Label=W_36
PF12.GPIO_PuPd=GPIO_PULLUP
PF12.Signal=GPIO_Input
PF13.GPIOParameters=GPIO_PuPd,GPIO_Label
PF13.GPIO_Label=E_37
PF13.GPIO_PuPd=GPIO_PULLUP
PF13.Signal=GPIO_Input
PF14.GPIOParameters=GPIO_PuPd,GPIO_Label
PF14.GPIO_Label=R_38
PF14.GPIO_PuPd=GPIO_PULLUP
PF14.Signal=GPIO_Input
PF15.GPIOParameters=GPIO_PuPd,GPIO_Label
PF15.GPIO_Label=T_39
PF15.GPIO_PuPd=GPIO_PULLUP
PF15.Signal=GPIO_Input
PF2.GPIOParameters=GPIO_PuPd,GPIO_Label
PF2.GPIO_Label=Key5_22
PF2.GPIO_PuPd=GPIO_PULLUP
PF2.Signal=GPIO_Input
PF3.GPIOParameters=GPIO_PuPd,GPIO_Label
PF3.GPIO_Label=F8_9
PF3.GPIO_PuPd=GPIO_PULLUP
PF3.Signal=GPIO_Input

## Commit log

2026-02-11 push required files
2026-02-11 push gerbers
2026-02-12 push
2026-02-13 Update 3d model and required footprints
2026-02-13 Made and added 3d case
2026-02-14 Added usb ports to pcb step
2026-02-14 Updated case 3d model to include usb ports and added photos of 3d models
2026-02-14 Added f3d files
2026-02-14 Added README.md
2026-02-14 Added prototype firmware and connected ground planes together on pcb
2026-02-14 Removed pcb backup folder
2026-02-14 Updated PCB screenshot to reflect connected gnd planes and set zone visibility to higher number
2026-02-22 Added siklscreen quote unquote art, i am not an artist okay?
2026-02-22 added temp image
2026-02-23 Added art in the empty space on case
